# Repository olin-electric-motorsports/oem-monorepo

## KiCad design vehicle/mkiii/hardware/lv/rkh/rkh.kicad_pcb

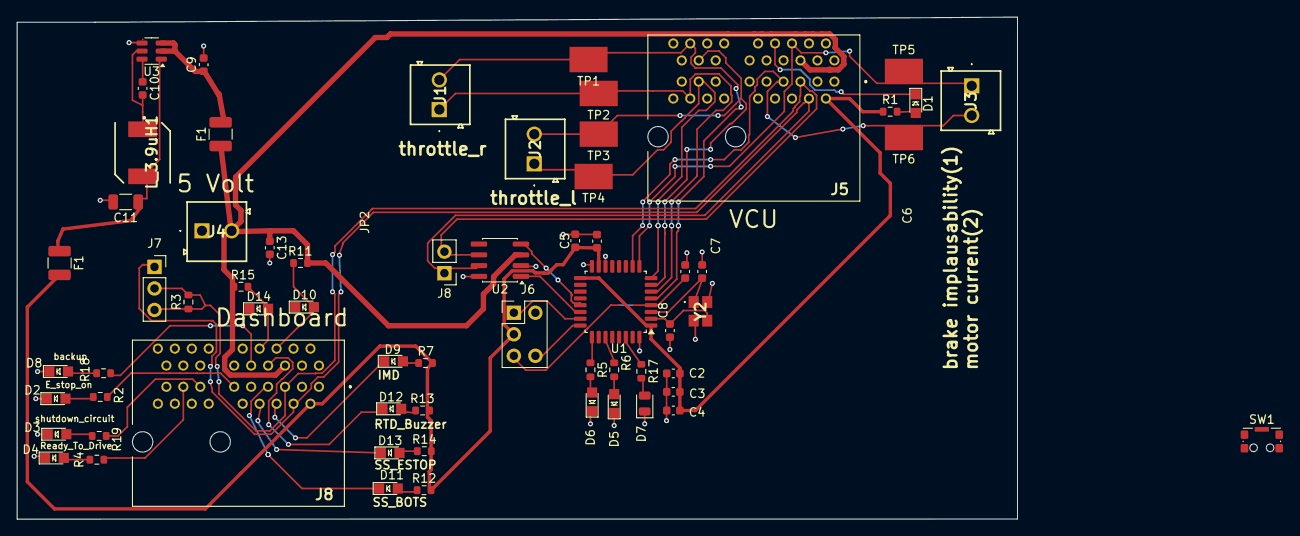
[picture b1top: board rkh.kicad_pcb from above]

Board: 2 copper layers, 118.0 x 59.2 mm, 64 parts (0 on the bottom side), 39 nets.

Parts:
C1: C_10nF_50V; C_0603_1608Metric
C2: C_0.47uF_25V; C_0603_1608Metric
C3, C4, C6, C10: C_0.1uF_16V; C_0603_1608Metric
C5: C_1uF_25V; C_0603_1608Metric
C7: 30pf; C_0603_1608Metric
C8: 30pF; C_0603_1608Metric
C9: C_10uF_10V; C_0603_1608Metric
C11: C_22uF_25V; C_1206_3216Metric
C13: 0u1F; C_0603_1608Metric
D1, D2, D3, D4, D8, D9, D10, D11, D12, D13, D14: LED; LED_0805_OEM
D5: LED_Motor_Current_Issue_If_On; LED_0805_OEM
D6: LED_break_implausability_if_on; LED_0805_OEM
D7: LED_Throttle_Issue_If_On; D_0805_2012Metric
F1, F1#2: F_500mA_16V; Fuse_1210_3225Metric
J1, J2, J3, J4: TWO_WIRE_SCREW_TERMINAL; TAD05021LG
J5: VCU_pinout; J_PCIe_x1
J6: J_Programming_Pin_Header; J_Programming_Pin_Header_Keyed
J7: Conn_01x03_Pin; PinSocket_1x03_P2.54mm_Vertical
J8: Conn_01x02_Pin; PinHeader_1x02_P2.54mm_Vertical
J8#2: Dashboard_PCIE; J_PCIe_x1
L_3.9uH1: L; SPM6530 (L_2.2uH_8.2A_19m_SMD - SPM6530T-2R2M)
R1, R2, R3, R4, R5, R6, R7, R11, R12, R13, R14, R15, R17, R18, R19: R_1k_0.1W; R_0603_1608Metric
SW1: CK_KMS2xxG; SW_SPST_CK_KMS2xxGP
TP1, TP2, TP3, TP4, TP5, TP6: TestPoint; Test_Point_SMD
U1: STM32G441KBT6; LQFP-32_7x7mm_P0.8mm
U2: MCP2561-E-SN; SOIC-8_3.9x4.9mm_P1.27mm
U3: AP63203WU-7; SOT-23-6
Y2: X_Crystal_GND24; FA238160000MBC0 (X_16MHz_18pF_SMD - FA-238_16.0000MB-C0)

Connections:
+3V3: C1.1, C2.1, C3.2, C4.2, C5.1, C11.1, F1.1, F1.2, J5.A2 (3.3V), J6.3, J8#2.A2 (3.3V), L_3.9uH1.2, R1.1, R7.1, R12.1, R13.1, R14.1, R15.1, U1.1 (VDD), U1.15 (VDDA), U1.17 (VDD), U3.1 (FB)
+5V: C9.1, C13.1, F1#2.2, J4.2, J5.B5 (5V), J8#2.B5 (5V), R11.1, U2.3 (VDD), U3.2 (EN), U3.3 (VIN)
/CAN_+: J5.A4 (CAN+), J7.1, J8.1, J8#2.A4 (CAN+), U2.7 (CANH)
/CAN_-: J5.A5 (CAN-), J7.2, J7.3, J8.2, J8#2.A5 (CAN-), R3.1, R3.2, U2.6 (CANL)
/CAN_RX: U1.21 ((FDCAN1_RX/GPIO_EXTI11)PA11), U2.4 (RXD)
/CAN_TX: U1.22 ((FDCAN1_TX/GPIO_EXTI12)PA12), U2.1 (TXD)
/NRST: C6.2, J6.4, U1.4 ((GPIO_EXTI10)PG10-NRST)
/SWCLK: J6.5, U1.24 ((SYS_JTCK-SWCLK/GPIO_EXTI14)PA14)
/SWDIO: J6.1, U1.23 ((SYS_JTMS-SWDIO/GPIO_EXTI13)PA13)
/break_pressure_sensor: J3.1, J5.B6 (io_1), TP5.1, U1.9 ((USART2_CK/TIM3_CH2/GPIO_EXTI4/ADC2_IN1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)
/motor_current_sense: J3.2, J5.A7 (io_2), TP6.1, U1.10 ((TIM2_ETR/TIM2_CH1/GPIO_EXTI5/ADC2_IN13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)
/throttle_l+: J2.1, J5.A15 (io_18), TP4.1, U1.8 ((TIM15_CH2/USART2_RX/TIM2_CH4/GPIO_EXTI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)
/throttle_l-: J2.2, J5.B15 (io_19), TP3.1, U1.7 ((TIM15_CH1/USART2_TX/TIM2_CH3/GPIO_EXTI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)
/throttle_r+: J1.1, J5.A16 (io_20), TP2.1, U1.6 ((TIM15_CH1N/TIM2_CH2/GPIO_EXTI1/ADC2_IN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)
/throttle_r-: J1.2, J5.B16 (io_21), TP1.1, U1.5 ((TIM2_ETR/TIM2_CH1/GPIO_EXTI0/ADC2_IN1/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)
GND: C1.2, C2.2, C3.1, C4.1, C5.2, C6.1, C7.2, C8.2, C9.2, C11.2, C13.2, D2.1 (K), D3.1 (K), D4.1 (K), D5.1 (K), D6.1 (K), D7.1 (K), D8.1 (K), J6.2, U1.14 (VSSA), U1.16 (VSS), U1.32 (VSS), U2.2 (VSS), U2.8 (STBY), U3.4 (GND), Y2.2, Y2.4
unnamed: D1.2 (A), R1.2
unnamed: D1.1 (K), J5.B8 (io_5)
unnamed: D2.2 (A), J8#2.A11 (io_10), R2.2
unnamed: D3.2 (A), J8#2.A13 (io_14), R19.2
unnamed: D4.2 (A), J8#2.A15 (io_18), R4.2
unnamed: D5.2 (A), R6.1, U1.27 ((TIM17_BKIN/SPI1_MISO/TIM3_CH1/TIM16_CH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)
unnamed: D6.2 (A), R5.1, U1.25 ((TIM2_ETR/TIM2_CH1/GPIO_EXTI15)PA15)
unnamed: D7.2 (A), R17.1, U1.30 ((TIM3_CH4/TIM4_CH2/TIM17_CH1N/GPIO_EXTI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)
unnamed: D8.2 (A), J8#2.B9 (io_7), R18.2
unnamed: D9.2 (A), R7.2
unnamed: D9.1 (K), J8#2.A6 (io_0)
unnamed: D10.2 (A), J8#2.B6 (io_1), R11.2
unnamed: D11.2 (A), R12.2
unnamed: D11.1 (K), J8#2.A7 (io_2)
unnamed: D12.2 (A), R13.2
unnamed: D12.1 (K), J8#2.B7 (io_3)
unnamed: D13.2 (A), J8#2.A8 (io_4), R14.2
unnamed: D14.2 (A), J8#2.B8 (io_5), R15.2
unnamed: C8.1, U1.2 (PF0-OSC_IN), Y2.3
unnamed: C7.1, U1.3 (PF1-OSC_OUT), Y2.1
unnamed: C10.1, U3.6 (BST)
unnamed: C10.2, L_3.9uH1.1, U3.5 (SW)
x: U1.19 ((TIM2_CH3/TIM15_BKIN/USART1_TX/GPIO_EXT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), U1.20 ((TIM2_CH4/USART1_RX/TIM17_BKIN/GPIO_EXT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), U1.28 ((TIM17_CH1/SPI1_MOSI/TIM3_CH2/TIM16_BKI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), U1.29 ((TIM4_CH1/TIM16_CH1N/GPIO_EXTI6)PB6), U1.31 ((TIM4_CH3/TIM16_CH1/GPIO_EXTI8)PB8-BOOT0)

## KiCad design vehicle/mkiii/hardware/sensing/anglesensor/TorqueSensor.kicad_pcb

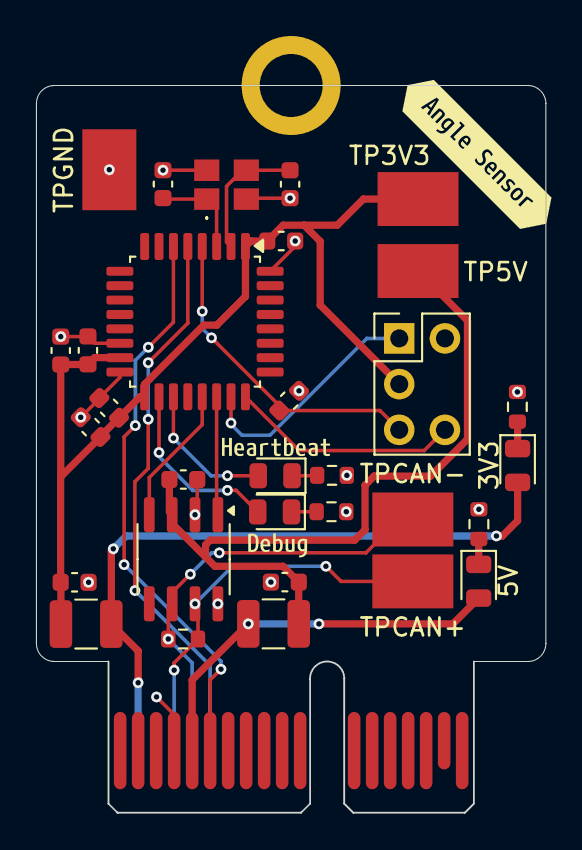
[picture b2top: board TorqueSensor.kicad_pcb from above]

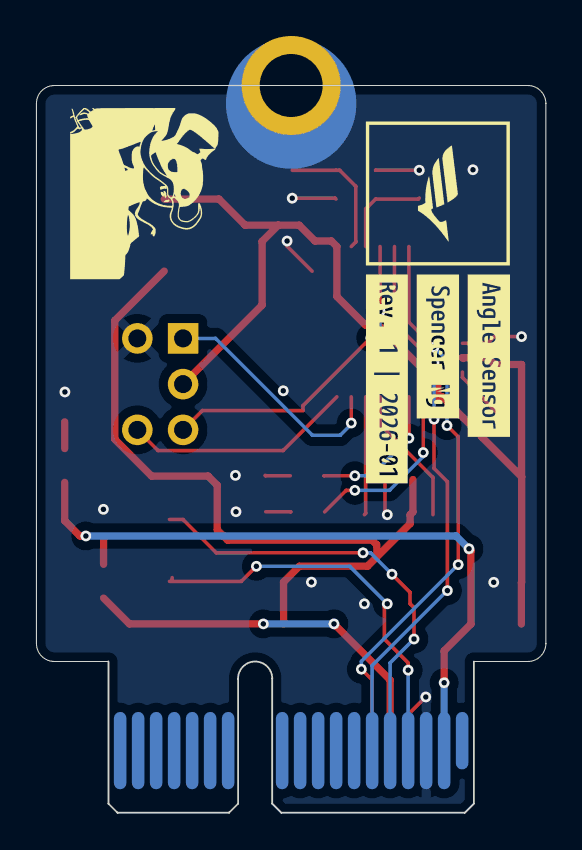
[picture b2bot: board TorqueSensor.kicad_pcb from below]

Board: 2 copper layers, 28.3 x 40.4 mm, 39 parts (3 on the bottom side), 22 nets.

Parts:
3V3, 5V: LED_WHITE; D_0805_2012Metric
C1: C_0.1uF_16V; C_0603_1608Metric
C2, C9: C_30pF_50V; C_0603_1608Metric
C3: C_4.7uF_25V; C_0603_1608Metric
C4, C5, C8: C_0.1uF_50V; C_0603_1608Metric
C6: C_1uF_50V; C_0603_1608Metric
C7: C_10nF_50V; C_0603_1608Metric
C10, C11: C_10uF_10V; C_0603_1608Metric
D1: LED_AMBER; D_0805_2012Metric
D2: LED_WHITE; D_0805_2012Metric
F1, F2: F_500mA_16V; Fuse_1210_3225Metric
H1: H_MountingHole
J1: J_PCIe_x1; J_PCIe_x1_Key
J2: J_Programming_Pin_Header; J_Programming_Pin_Header_Keyed
R1, R3, R4, R5: R_1k; R_0603_1608Metric
R2: R_120; R_0603_1608Metric
TP3V3, TP5V: TP_SMD; TP_Hook_SMD
TPCAN+: TP_SMD; TP_Hook_SMD
TPCAN-: TP_SMD; TP_Hook_SMD
TPGND: TP_SMD; TP_Hook_SMD
U2: STM32G441KBT6; LQFP-32_7x7mm_P0.8mm
U3: MCP2561-E_SN; SOIC-8_3.9x4.9mm_P1.27mm
Y1: X_16MHz_18pF; FA238160000MBC0 (X_16MHz_18pF_SMD - FA-238_16.0000MB-C0)
kibuzzard-697FF3E2: G***; kibuzzard-697FF3E2
kibuzzard-697FF3F7: G***; kibuzzard-697FF3F7
kibuzzard-697FF4A8: G***; kibuzzard-697FF4A8
kibuzzard-697FF7D3: G***; kibuzzard-697FF7D3
kibuzzard-697FF82D: G***; kibuzzard-697FF82D
kibuzzard-697FF937: G***; kibuzzard-697FF937

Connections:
+3V3: C3.1, C4.1, C5.1, C6.1, C7.1, C10.1, F1.1, J2.3, TP3V3.1, U2.1 (VDD), U2.15 (VDDA), U2.17 (VDD)
+5V: C1.1, C11.1, F2.1, TP5V.1, U3.3 (VDD)
/CAN_+: J1.A4 (CAN+), R2.2, TPCAN+.1, U3.7 (CANH)
/CAN_-: J1.A5 (CAN-), R2.1, TPCAN-.1, U3.6 (CANL)
/CAN_RX: U2.21 ((FDCAN1_RX/GPIO_EXTI11)PA11), U3.4 (RXD)
/CAN_TX: U2.22 ((FDCAN1_TX/GPIO_EXTI12)PA12), U3.1 (TXD)
/DEBUG_LED: D1.2 (A), U2.18 ((TIM4_ETR/USART1_CK/GPIO_EXTI8)PA8)
/HEARTBEAT_LED: D2.2 (A), U2.19 ((TIM2_CH3/TIM15_BKIN/USART1_TX/GPIO_EXT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)
/NRST: C8.1, J2.4, U2.4 ((GPIO_EXTI10)PG10-NRST)
/PWM_Input: J1.A6 (io_0), U2.5 ((TIM2_ETR/TIM2_CH1/GPIO_EXTI0/ADC2_IN1/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)
/SWCLK: J2.5, U2.24 ((SYS_JTCK-SWCLK/GPIO_EXTI14)PA14)
/SWDIO: J2.1, U2.23 ((SYS_JTMS-SWDIO/GPIO_EXTI13)PA13)
/Status_Signal_Input: J1.B6 (io_1), U2.6 ((TIM15_CH1N/TIM2_CH2/GPIO_EXTI1/ADC2_IN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)
GND: C1.2, C2.2, C3.2, C4.2, C5.2, C6.2, C7.2, C8.2, C9.2, C10.2, C11.2, H1.1, J1.A3 (GND), J1.B4 (GND), J2.2, R1.2, R3.2, R4.2, R5.2, TPGND.1, U2.14 (VSSA), U2.16 (VSS), U2.32 (VSS), U3.2 (VSS), U3.8 (STBY), Y1.2, Y1.4
unnamed: D1.1 (K), R3.1
unnamed: D2.1 (K), R4.1
unnamed: 3V3.2 (A), F1.2, J1.A2 (3.3V)
unnamed: 3V3.1 (K), R1.1
unnamed: 5V.2 (A), F2.2, J1.B5 (5V)
unnamed: 5V.1 (K), R5.1
unnamed: C9.1, U2.2 (PF0-OSC_IN), Y1.3
unnamed: C2.1, U2.3 (PF1-OSC_OUT), Y1.1

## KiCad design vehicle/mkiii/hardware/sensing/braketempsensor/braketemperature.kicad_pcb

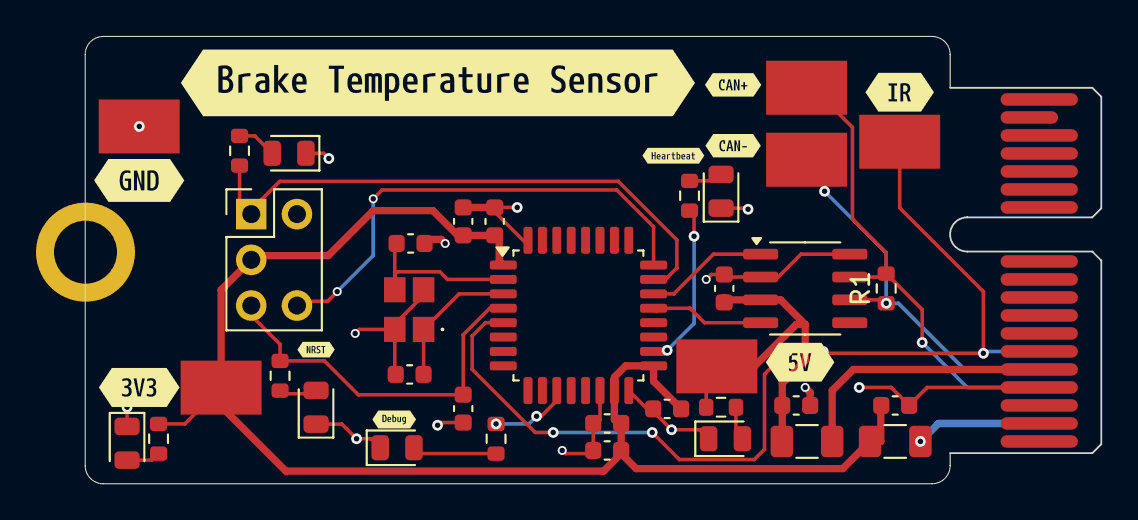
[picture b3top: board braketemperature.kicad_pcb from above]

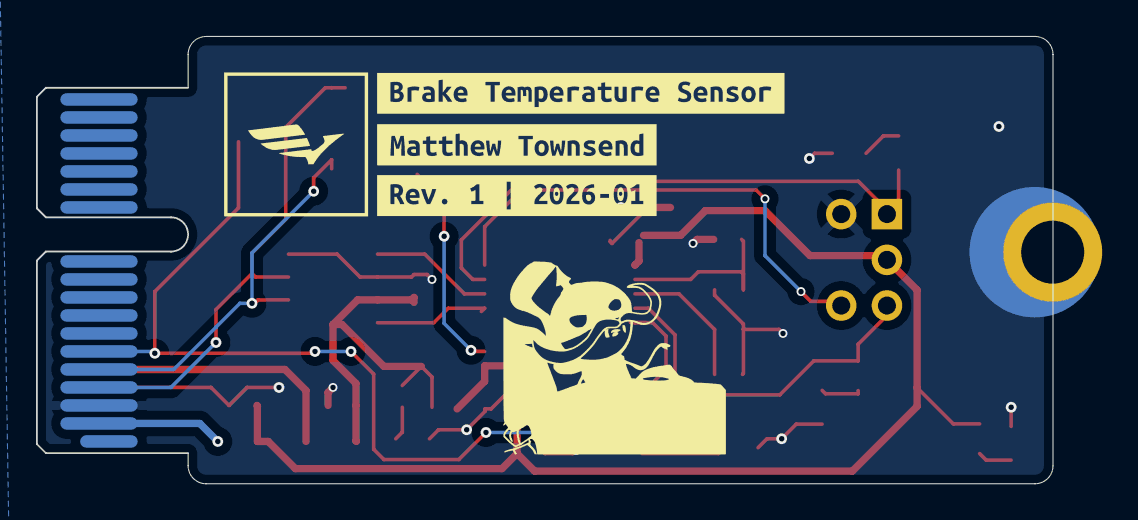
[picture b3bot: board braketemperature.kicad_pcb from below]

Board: 2 copper layers, 56.4 x 24.9 mm, 51 parts (3 on the bottom side), 23 nets.

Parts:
C1, C2, C4, C7: C_0.1uF; C_0603_1608Metric
C3: C_10nF; C_0603_1608Metric
C5: C_1uF; C_0603_1608Metric
C6: C_4.7uF; C_0603_1608Metric
C8, C9: C_30pF; C_0603_1608Metric
C10, C11: C_10uF_10V; C_0603_1608Metric
D1, D2, D3, D4, D5, D6: D_Red_LED; D_0805_2012Metric
F1, F2: F_500mA_8V; Fuse_1206_3216Metric
H1: H_MountingHole
J1: J_PCIe_x1; J_PCIe_x1_Key
J2: J_Programming_Pin_Header; J_Programming_Pin_Header_Keyed
R1: R_120; R_0603_1608Metric
R2, R3, R4, R5, R6, R7: R_1k; R_0603_1608Metric
TP1, TP2, TP3, TP4, TP5, TP6: TP_SMD; TP_Hook_SMD
U1: MCP2561-E_SN; SOIC-8_3.9x4.9mm_P1.27mm
U2: STM32G441KBT6; LQFP-32_7x7mm_P0.8mm
Y1: X_16MHz_18pF; FA238160000MBC0 (X_16MHz_18pF_SMD - FA-238_16.0000MB-C0)
kibuzzard-697E6E94: G***; kibuzzard-697E6E94
kibuzzard-697E6EEF: G***; kibuzzard-697E6EEF
kibuzzard-697E6F70: G***; kibuzzard-697E6F70
kibuzzard-697E6FE4: G***; kibuzzard-697E6FE4
kibuzzard-697F80A9: G***; kibuzzard-697F80A9
kibuzzard-697F80BA: G***; kibuzzard-697F80BA
kibuzzard-697F802E: G***; kibuzzard-697F802E
kibuzzard-69815F9D: G***; kibuzzard-69815F9D
kibuzzard-69815FEC: G***; kibuzzard-69815FEC
kibuzzard-69815FF8: G***; kibuzzard-69815FF8
kibuzzard-69816079: G***; kibuzzard-69816079
kibuzzard-69816083: G***; kibuzzard-69816083
kibuzzard-69816091: G***; kibuzzard-69816091

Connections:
+3V3: C2.1, C3.1, C4.1, C5.1, C6.1, C11.1, F2.1, J2.3, R3.1, TP3.1, U2.1 (VDD), U2.15 (VDDA), U2.17 (VDD)
+5V: C1.1, C10.1, F1.1, R2.1, TP2.1, U1.3 (VDD)
/CAN_RX: U1.4 (RXD), U2.21 ((FDCAN1_RX/GPIO_EXTI11)PA11)
/CAN_TX: U1.1 (TXD), U2.22 ((FDCAN1_TX/GPIO_EXTI12)PA12)
/Debug LED: R5.1, U2.11 ((TIM3_CH1/TIM16_CH1/GPIO_EXTI6/ADC2_IN3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)
/Heartbeat LED: R4.1, U2.18 ((TIM4_ETR/USART1_CK/GPIO_EXTI8)PA8)
/IR Output - PA0: J1.A6 (io_0), TP1.1, U2.5 ((TIM2_ETR/TIM2_CH1/GPIO_EXTI0/ADC2_IN1/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)
/NRST: C7.1, J2.4, R6.1, U2.4 ((GPIO_EXTI10)PG10-NRST)
/SWCLK: J2.5, U2.24 ((SYS_JTCK-SWCLK/GPIO_EXTI14)PA14)
/SWDIO: J2.1, R7.1, U2.23 ((SYS_JTMS-SWDIO/GPIO_EXTI13)PA13)
GND: C1.2, C2.2, C3.2, C4.2, C5.2, C6.2, C7.2, C8.2, C9.2, C10.2, C11.2, D1.1 (K), D2.1 (K), D3.1 (K), D4.1 (K), D5.1 (K), D6.1 (K), H1.1, J1.A3 (GND), J1.B4 (GND), J2.2, TP6.1, U1.2 (VSS), U1.8 (STBY), U2.14 (VSSA), U2.16 (VSS), U2.32 (VSS), Y1.2, Y1.4
unnamed: D1.2 (A), R2.2
unnamed: D2.2 (A), R3.2
unnamed: D3.2 (A), R4.2
unnamed: D4.2 (A), R5.2
unnamed: D5.2 (A), R6.2
unnamed: D6.2 (A), R7.2
unnamed: F2.2, J1.A2 (3.3V)
unnamed: F1.2, J1.B5 (5V)
unnamed: J1.A4 (CAN+), R1.2, TP4.1, U1.7 (CANH)
unnamed: J1.A5 (CAN-), R1.1, TP5.1, U1.6 (CANL)
unnamed: C9.1, U2.2 (PF0-OSC_IN), Y1.3
unnamed: C8.1, U2.3 (PF1-OSC_OUT), Y1.1

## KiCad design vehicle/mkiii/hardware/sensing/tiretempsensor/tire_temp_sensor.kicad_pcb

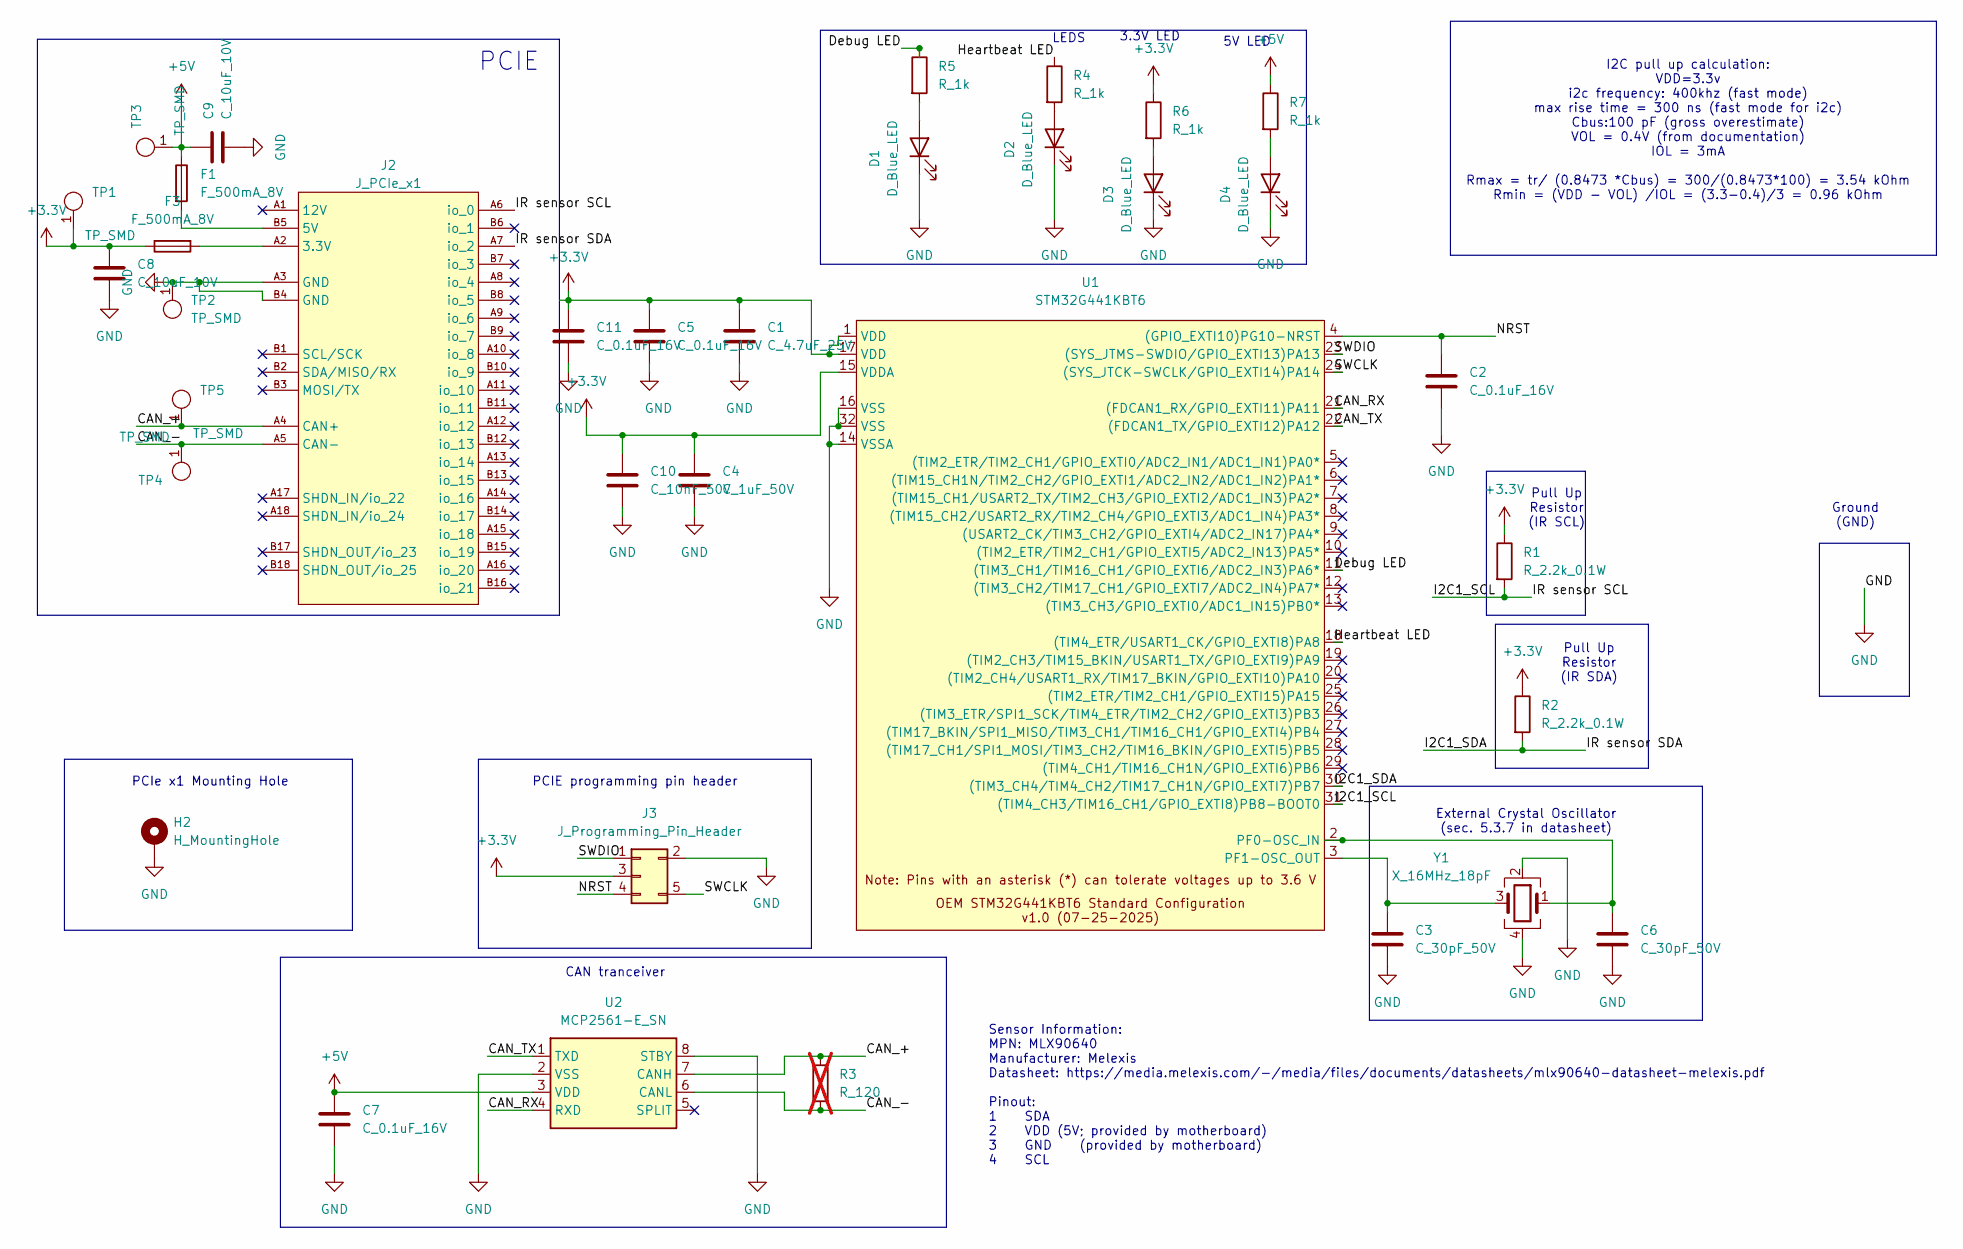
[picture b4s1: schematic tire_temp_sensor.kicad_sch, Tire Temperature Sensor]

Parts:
C1: C_4.7uF_25V; C_0603_1608Metric; MPN GRT188R61E475ME13D
C2, C5, C7, C11: C_0.1uF_16V; C_0603_1608Metric; MPN C0603C104Z4VACTU
C3, C6: C_30pF_50V; C_0603_1608Metric; MPN CML0603C0G300JT50V
C4: C_1uF_50V; C_0603_1608Metric; MPN UMK107BJ105KA-T
C8, C9: C_10uF_10V; C_0603_1608Metric; MPN GRM188D71A106KA73D
C10: C_10nF_50V; C_0603_1608Metric; MPN CL10B103KB8NNNC
D1, D2, D3, D4: D_Blue_LED; D_0805_2012Metric; MPN LTST-C171TBKT
F1, F3: F_500mA_8V; Fuse_1206_3216Metric; MPN 0ZCJ0050FF2G
H2: H_MountingHole
J2: J_PCIe_x1; J_PCIe_x1_Key; MPN 2-1761465-1
J3: J_Programming_Pin_Header; J_Programming_Pin_Header_Keyed
R1, R2: R_2.2k_0.1W; R_0603_1608Metric; MPN WR06X222 JTL
R3: R_120; R_0603_1608Metric; MPN RC0603FR-13120RL; not fitted
R4, R5, R6, R7: R_1k; R_0603_1608Metric; MPN RMCF0603FT1K00 (or ERJ-3GEYJ102V)
TP1, TP2, TP3, TP4, TP5: TP_SMD; TP_Hook_SMD; MPN 5019
U1: STM32G441KBT6; LQFP-32_7x7mm_P0.8mm
U2: MCP2561-E_SN; SOIC-8_3.9x4.9mm_P1.27mm; MPN MCP2561-E/SN
Y1: X_16MHz_18pF; FA238160000MBC0 (X_16MHz_18pF_SMD - FA-238_16.0000MB-C0); MPN FA-238 16.0000MB-C0

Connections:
+3.3V: C1.1, C4.1, C5.1, C8.1, C10.1, C11.1, F3.1, J3.3, R1.1, R2.1, R6.1, TP1.1, U1.1 (VDD), U1.15 (VDDA), U1.17 (VDD)
+5V: C7.1, C9.1, F1.1, R7.1, TP3.1, U2.3 (VDD)
/CAN_+: J2.A4 (CAN+), R3.1, TP5.1, U2.7 (CANH)
/CAN_-: J2.A5 (CAN-), R3.2, TP4.1, U2.6 (CANL)
/CAN_RX: U1.21 ((FDCAN1_RX/GPIO_EXTI11)PA11), U2.4 (RXD)
/CAN_TX: U1.22 ((FDCAN1_TX/GPIO_EXTI12)PA12), U2.1 (TXD)
/Debug LED: R5.1, U1.11 ((TIM3_CH1/TIM16_CH1/GPIO_EXTI6/ADC2_IN3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)
/Heartbeat LED: R4.1, U1.18 ((TIM4_ETR/USART1_CK/GPIO_EXTI8)PA8)
/I2C1_SCL: J2.A6 (io_0), R1.2, U1.31 ((TIM4_CH3/TIM16_CH1/GPIO_EXTI8)PB8-BOOT0)
/I2C1_SDA: J2.A7 (io_2), R2.2, U1.30 ((TIM3_CH4/TIM4_CH2/TIM17_CH1N/GPIO_EXTI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)
/NRST: C2.1, J3.4, U1.4 ((GPIO_EXTI10)PG10-NRST)
/SWCLK: J3.5, U1.24 ((SYS_JTCK-SWCLK/GPIO_EXTI14)PA14)
/SWDIO: J3.1, U1.23 ((SYS_JTMS-SWDIO/GPIO_EXTI13)PA13)
GND: C1.2, C2.2, C3.2, C4.2, C5.2, C6.2, C7.2, C8.2, C9.2, C10.2, C11.2, D1.1 (K), D2.1 (K), D3.1 (K), D4.1 (K), H2.1, J2.A3 (GND), J2.B4 (GND), J3.2, TP2.1, U1.14 (VSSA), U1.16 (VSS), U1.32 (VSS), U2.2 (VSS), U2.8 (STBY), Y1.2, Y1.4
unnamed: D1.2 (A), R5.2
unnamed: D2.2 (A), R4.2
unnamed: D3.2 (A), R6.2
unnamed: D4.2 (A), R7.2
unnamed: F3.2, J2.A2 (3.3V)
unnamed: F1.2, J2.B5 (5V)
unnamed: C6.1, U1.2 (PF0-OSC_IN), Y1.1
unnamed: C3.1, U1.3 (PF1-OSC_OUT), Y1.3

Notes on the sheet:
PCIE programming pin header
PCIe x1 Mounting Hole
I2C pull up calculation: VDD=3.3v i2c frequency: 400khz (fast mode) max rise time = 300 ns (fast mode for i2c) Cbus:100 pF (gross overestimate) VOL = 0.4V (from documentation) IOL = 3mA Rmax = tr/ (0.8473 *Cbus) = 300/(0.8473*100) = 3.54 kOhm Rmin = (VDD - VOL) /IOL = (3.3-0.4)/3 = 0.96 kOhm
External Crystal Oscillator (sec. 5.3.7 in datasheet)
PCIE
Ground (GND)
5V LED
3.3V LED
CAN tranceiver
Pull Up Resistor (IR SDA)
Pull Up Resistor (IR SCL)
Sensor Information: MPN: MLX90640 Manufacturer: Melexis Datasheet: https://media.melexis.com/-/media/files/documents/datasheets/mlx90640-datasheet-melexis.pdf Pinout: 1 SDA 2 VDD (5V; provided by motherboard) 3 GND (provided by motherboard) 4 SCL
LEDS

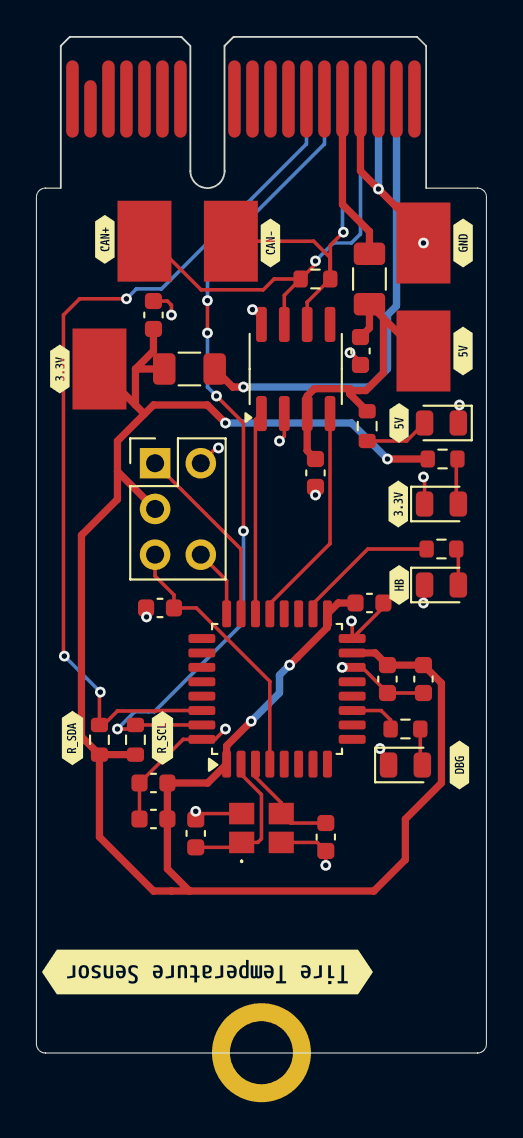
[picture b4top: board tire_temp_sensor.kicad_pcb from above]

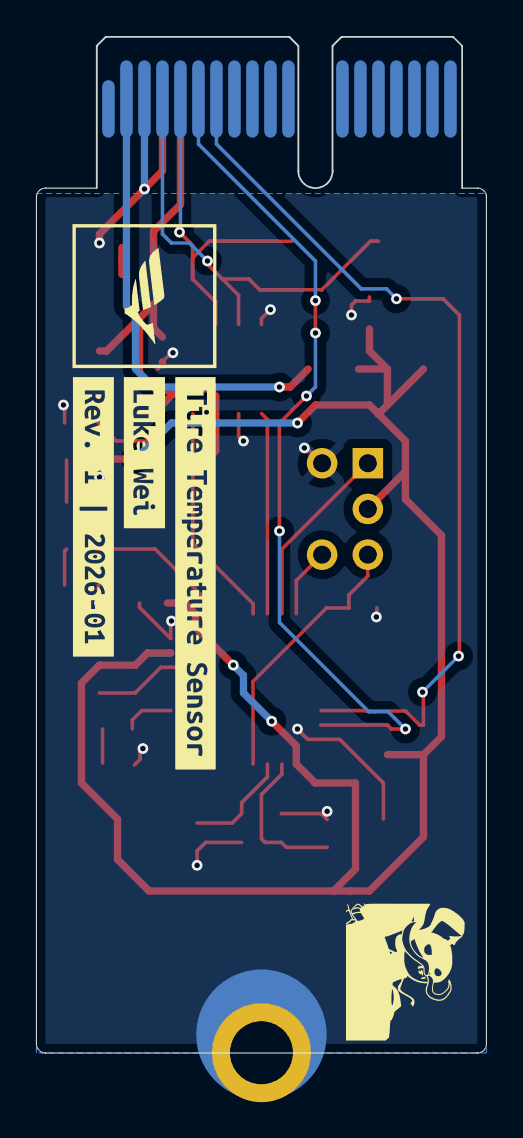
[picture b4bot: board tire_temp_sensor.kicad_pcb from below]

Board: 2 copper layers, 25.0 x 56.5 mm, 50 parts (3 on the bottom side), 22 nets.

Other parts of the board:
kibuzzard-697E5AB9: G***; kibuzzard-697E5AB9
kibuzzard-697E5B7C: G***; kibuzzard-697E5B7C
kibuzzard-697E5B13: G***; kibuzzard-697E5B13
kibuzzard-697E5B64: G***; kibuzzard-697E5B64
kibuzzard-697E5B74: G***; kibuzzard-697E5B74
kibuzzard-697E5BB9: G***; kibuzzard-697E5BB9
kibuzzard-697E5C85: G***; kibuzzard-697E5C85
kibuzzard-697E5DCC: G***; kibuzzard-697E5DCC
kibuzzard-697E5E44: G***; kibuzzard-697E5E44
kibuzzard-697E730B: G***; kibuzzard-697E730B
kibuzzard-6980A3A7: G***; kibuzzard-6980A3A7
kibuzzard-6980A425: G***; kibuzzard-6980A425
kibuzzard-6980A498: G***; kibuzzard-6980A498
kibuzzard-698147C7: G***; kibuzzard-698147C7
kibuzzard-69814769: G***; kibuzzard-69814769

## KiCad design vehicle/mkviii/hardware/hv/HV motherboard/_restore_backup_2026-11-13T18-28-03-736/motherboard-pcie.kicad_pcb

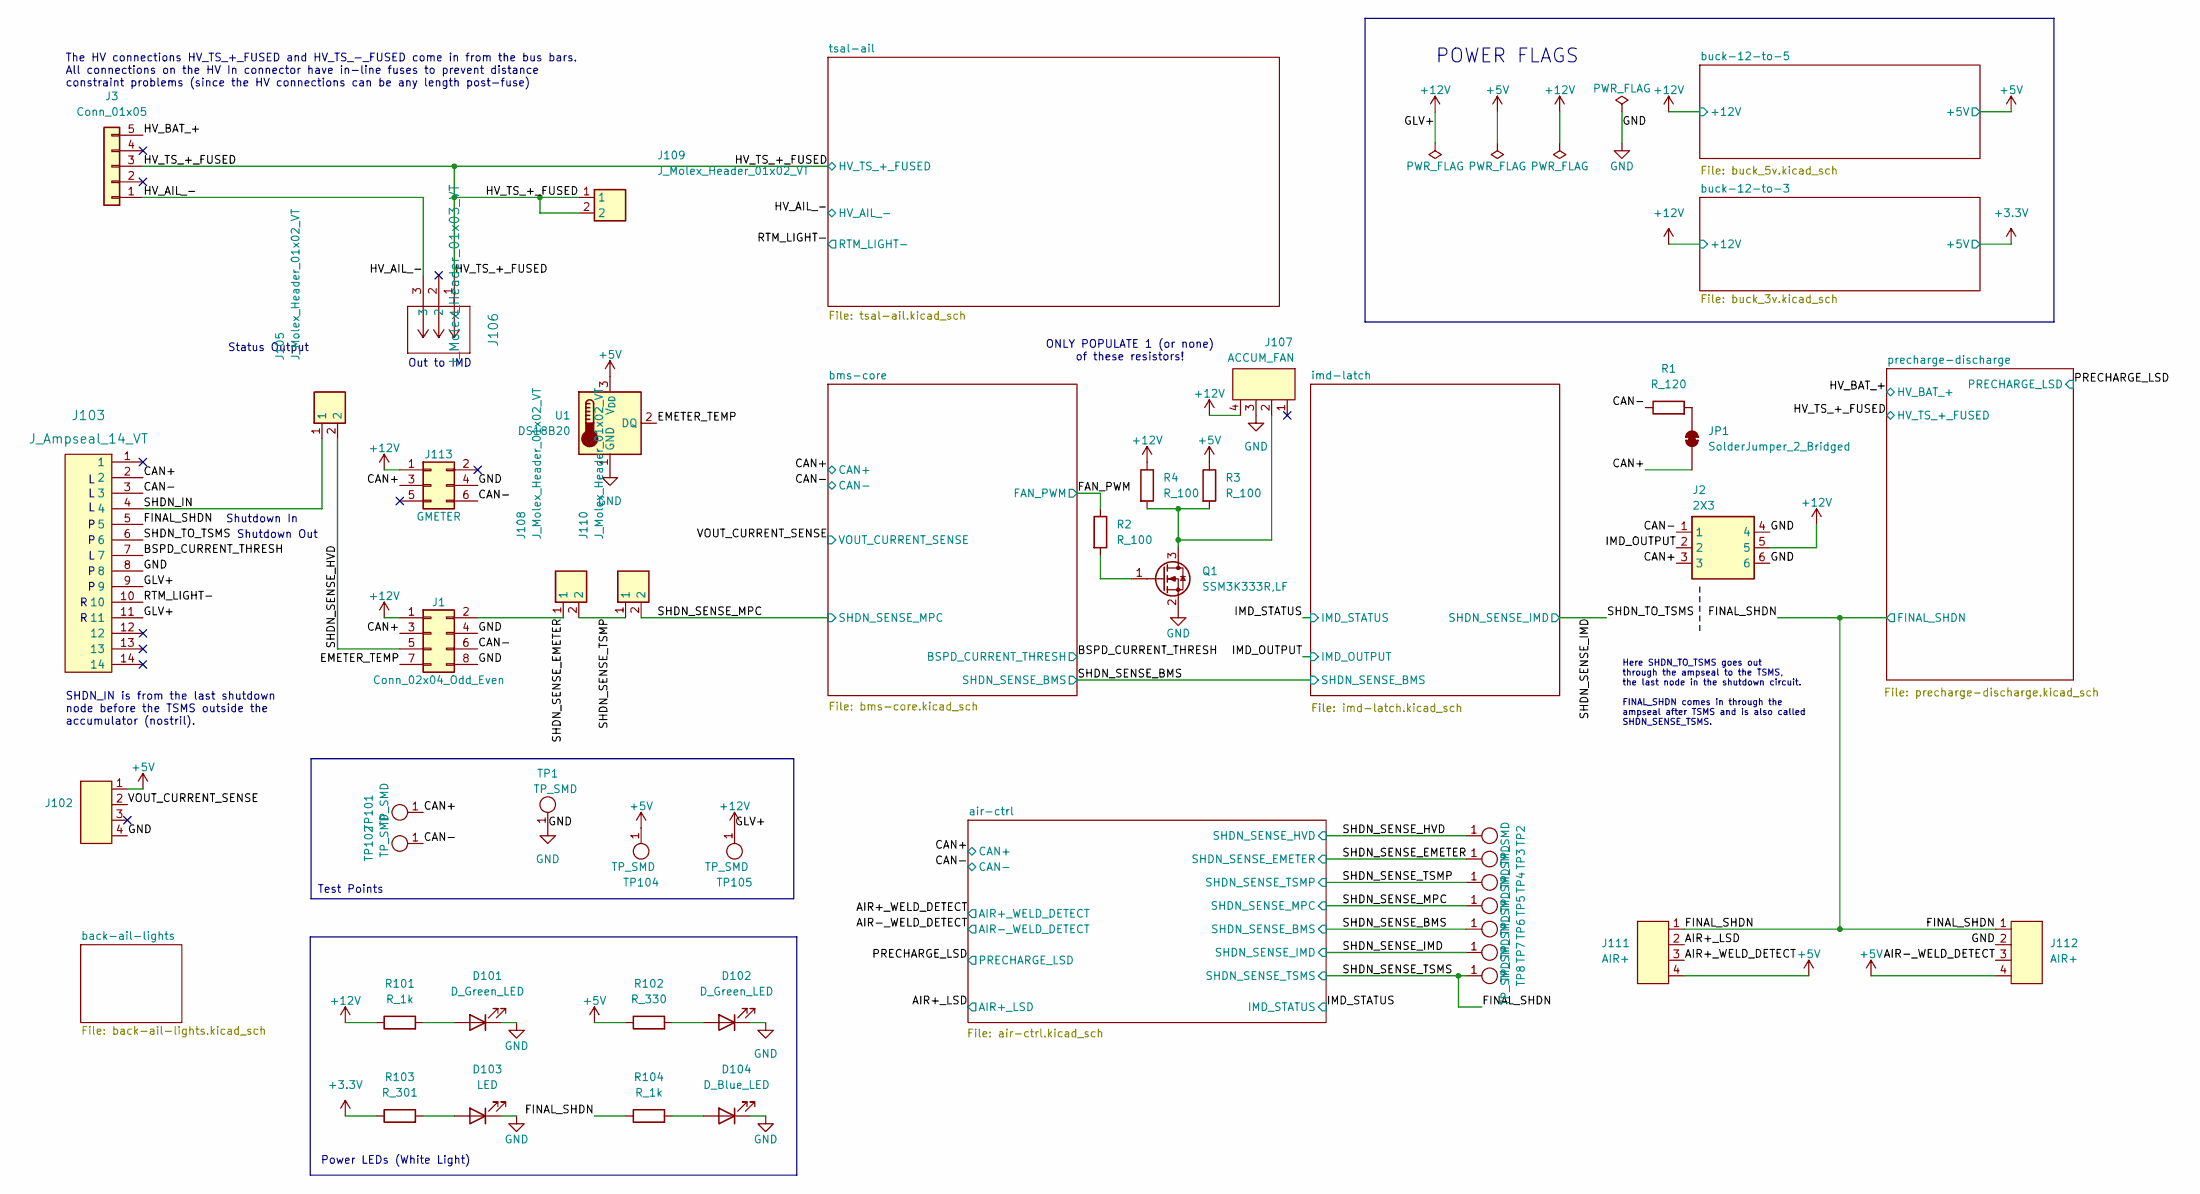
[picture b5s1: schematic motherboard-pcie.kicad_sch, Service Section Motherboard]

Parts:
D101, D102: D_Green_LED; D_0805_2012Metric; MPN LTST-C170KGKT
D103: LED; D_0805_2012Metric; MPN QBLP631-IW
D104: D_Blue_LED; D_0805_2012Metric; MPN LTST-C171TBKT
J1: Conn_02x04_Odd_Even
J2: 2X3; J_Molex_Header_02x03_VT - 43045-06YY_121314; MPN 43045-0614
J3: Conn_01x05
J102, J111, J112: AIR+; J_Molex_Header_02x02_VT - 0430450414; MPN 430450414
J103: J_Ampseal_14_VT; MPN 1-776261-1
J105, J108, J109, J110: J_Molex_Header_01x02_VT; J_Molex_Header_01x02_VT - 43045-02YY_121314; MPN 43045-0212
J106: J_Molex_Header_01x03_VT; J_Molex_Header_01x03_VT - 436500327
J107: ACCUM_FAN; J_Molex_Header_02x02_VT - 0430450414; MPN 430450414
J113: GMETER
JP1: SolderJumper_2_Bridged
Q1: SSM3K333R,LF; SOT-23-3
R1: R_120; R_0603_1608Metric; MPN RC0603FR-13120RL
R2, R3, R4: R_100; R_0603_1608Metric; MPN RMCF0603FT100R
R101, R104: R_1k; R_0603_1608Metric; MPN RMCF0603FT1K00 (or ERJ-3GEYJ102V)
R102: R_330; R_0603_1608Metric; MPN RMCF0603FT330R (or WR06X3300FTL)
R103: R_301; R_0603_1608Metric; MPN CR0603-FX-3010ELF
TP1, TP2, TP3, TP4, TP5, TP6, TP7, TP8, TP101, TP102, TP104, TP105: TP_SMD; TP_Hook_SMD; MPN 5019
U1: DS18B20; TO-92_Inline

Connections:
+3.3V: R103.1; also elsewhere on the board
+5V: J102.1, J111.4, J112.4, R3.1, R102.1, TP104.1, U1.3 (V_{DD}); also elsewhere on the board
/AIR+_LSD: J111.2; also elsewhere on the board
/AIR+_WELD_DETECT: J111.3; also elsewhere on the board
/AIR-_WELD_DETECT: J112.3; also elsewhere on the board
/BSPD_CURRENT_THRESH: J103.7; also elsewhere on the board
/CAN+: J1.3, J2.3, J103.2, J113.3, JP1.1 (A), TP101.1; also elsewhere on the board
/CAN-: J1.6, J2.1, J103.3, J113.6, R1.1, TP102.1; also elsewhere on the board
/EMETER_TEMP: J1.7, U1.2 (DQ)
/FAN_PWM: R2.1; also elsewhere on the board
/FINAL_SHDN: J103.5, J111.1, J112.1, R104.1, TP8.1; also elsewhere on the board
/HV_AIL_-: J3.1, J106.3; also elsewhere on the board
/HV_BAT_+: J3.5; also elsewhere on the board
/HV_TS_+_FUSED: J3.3, J106.1, J109.1, J109.2; also elsewhere on the board
/IMD_OUTPUT: J2.2; also elsewhere on the board
/RTM_LIGHT-: J103.10; also elsewhere on the board
/SHDN_IN: J103.4, J105.1
/SHDN_SENSE_BMS: TP6.1; also elsewhere on the board
/SHDN_SENSE_EMETER: J1.2, J108.1, TP3.1; also elsewhere on the board
/SHDN_SENSE_HVD: J1.5, J105.2, TP2.1; also elsewhere on the board
/SHDN_SENSE_IMD: J103.6, TP7.1; also elsewhere on the board
/SHDN_SENSE_MPC: J110.2, TP5.1; also elsewhere on the board
/SHDN_SENSE_TSMP: J108.2, J110.1, TP4.1; also elsewhere on the board
/VOUT_CURRENT_SENSE: J102.2; also elsewhere on the board
unnamed: D101.2 (A), R101.2
unnamed: D102.2 (A), R102.2
unnamed: D103.2 (A), R103.2
unnamed: D104.2 (A), R104.2
unnamed: JP1.2 (B), R1.2
unnamed: J107.2, Q1.3 (D), R3.2, R4.2
unnamed: Q1.1 (G), R2.2

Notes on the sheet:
SHDN_IN is from the last shutdown node before the TSMS outside the accumulator (nostril).
Shutdown Out
Test Points
Shutdown In
Here SHDN_TO_TSMS goes out through the ampseal to the TSMS, the last node in the shutdown circuit. FINAL_SHDN comes in through the ampseal after TSMS and is also called SHDN_SENSE_TSMS.
Power LEDs (White Light)
POWER FLAGS
Status Output
ONLY POPULATE 1 (or none) of these resistors!
Out to IMD
The HV connections HV_TS_+_FUSED and HV_TS_-_FUSED come in from the bus bars. All connections on the HV In connector have in-line fuses to prevent distance constraint problems (since the HV connections can be any length post-fuse)

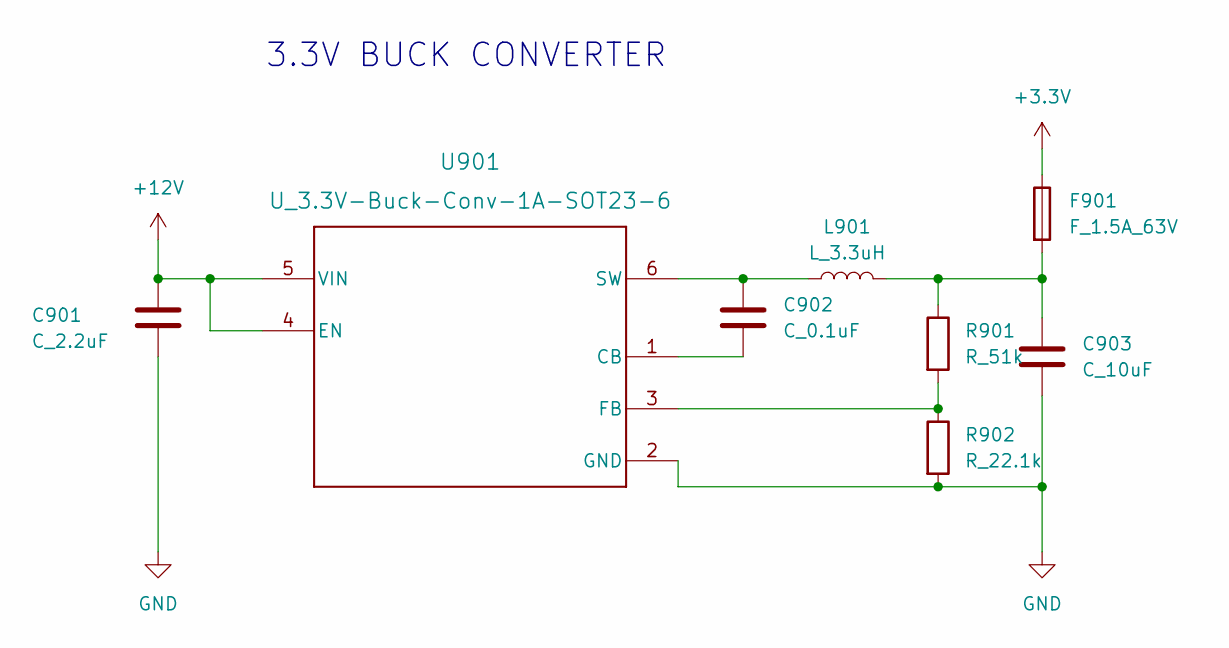
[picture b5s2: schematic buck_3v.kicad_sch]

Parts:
C901: C_2.2uF; C_0603_1608Metric; MPN GRM188R61E225KA12J
C902: C_0.1uF; C_0603_1608Metric; MPN C0603C104Z4VACTU
C903: C_10uF; C_0603_1608Metric; MPN GRM188D71A106KA73D
F901: F_1.5A_63V; Fuse_1206_3216Metric; MPN 046601.5NR
L901: L_3.3uH; SRN6045TA330M (L_3.3uH_5A_21m_SMD - SRN6045TA-3R3Y); MPN SRN6045TA-3R3Y
R901: R_51k; R_0603_1608Metric; MPN RMCF0603FT49K9
R902: R_22.1k; R_0603_1608Metric; MPN RMCF0603FT23K7
U901: U_3.3V-Buck-Conv-1A-SOT23-6; DBV0006A-IPC_A

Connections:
+3.3V: F901.1; also elsewhere on the board
unnamed: C903.1, F901.2, L901.2, R901.1
unnamed: C902.2, U901.1 (CB)
unnamed: R901.2, R902.1, U901.3 (FB)
unnamed: C902.1, L901.1, U901.6 (SW)

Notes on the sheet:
3.3V BUCK CONVERTER

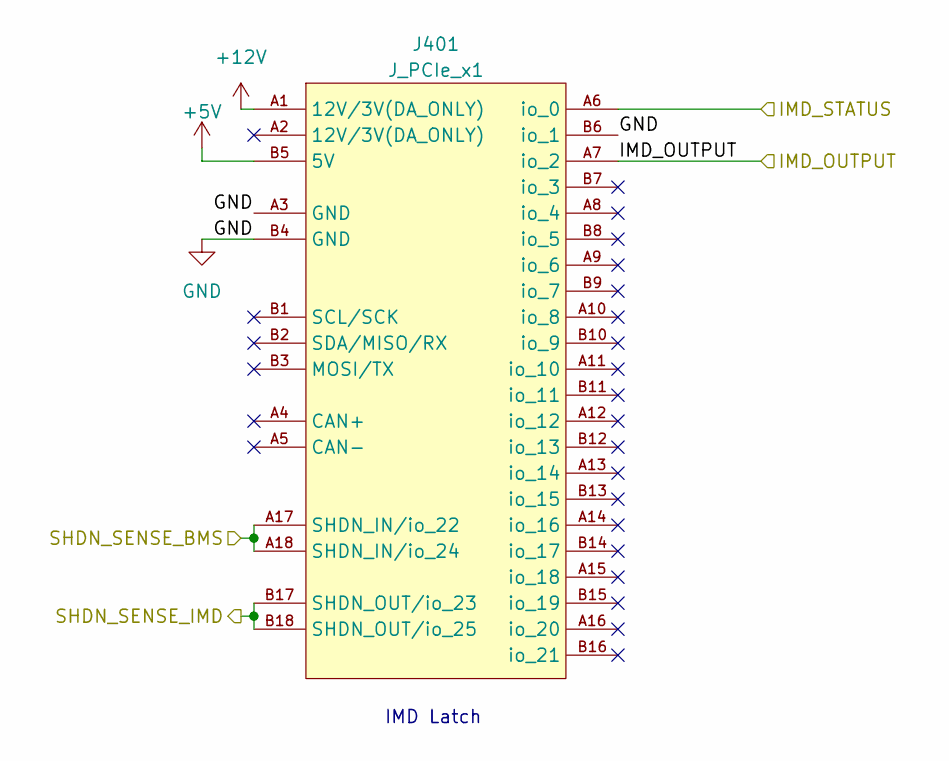
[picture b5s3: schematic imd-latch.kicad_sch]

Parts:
J401: J_PCIe_x1; MPN 2-1761465-1

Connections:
+5V: J401.B5 (5V); also elsewhere on the board
/IMD_OUTPUT: J401.A7 (io_2); also elsewhere on the board
/IMD_STATUS: J401.A6 (io_0); also elsewhere on the board
/SHDN_SENSE_BMS: J401.A17 (SHDN_IN/io_22), J401.A18 (SHDN_IN/io_24); also elsewhere on the board
/SHDN_SENSE_IMD: J401.B17 (SHDN_OUT/io_23), J401.B18 (SHDN_OUT/io_25); also elsewhere on the board

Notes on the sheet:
IMD Latch

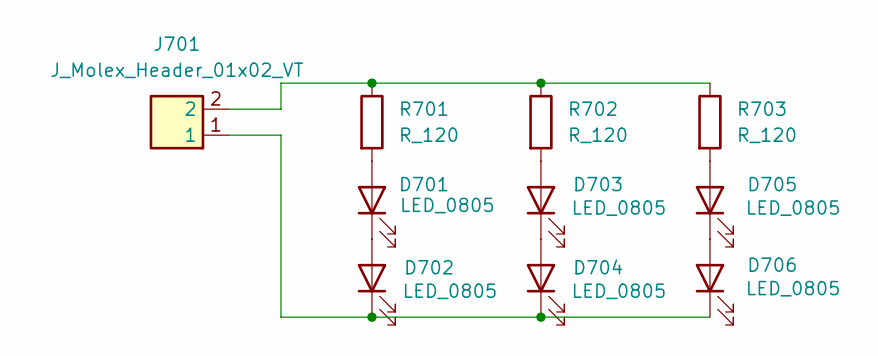
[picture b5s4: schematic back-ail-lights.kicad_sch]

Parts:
D701, D702, D703, D704, D705, D706: LED_0805; D_0805_2012Metric; MPN LTST-C170KGKT
J701: J_Molex_Header_01x02_VT; J_Molex_Header_01x02_VT - 43045-02YY_121314; MPN 43045-0212
R701, R702, R703: R_120; R_0603_1608Metric; MPN RC0603FR-13120RL

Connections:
unnamed: D701.2 (A), R701.2
unnamed: D701.1 (K), D702.2 (A)
unnamed: D702.1 (K), D704.1 (K), D706.1 (K), J701.1
unnamed: D703.2 (A), R702.2
unnamed: D703.1 (K), D704.2 (A)
unnamed: D705.2 (A), R703.2
unnamed: D705.1 (K), D706.2 (A)
unnamed: J701.2, R701.1, R702.1, R703.1
